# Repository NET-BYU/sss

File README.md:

# Seven Segment Sign

## Welcome to the Seven Segment Sign! (SSS)

## Getting Started
Here are some helpful links to get you up and running!
- [API Docs](https://sss.readthedocs.io/en/latest/API/Display/)
- [Install on Linux/Mac](https://sss.readthedocs.io/en/latest/Installation/Install%20SSS%20on%20Mac%20or%20Linux/)
- [Install on Windows](https://sss.readthedocs.io/en/latest/Installation/Install%20SSS%20on%20Windows/)
- [Create your first demo](https://sss.readthedocs.io/en/latest/Tutorials/Creating%20a%20demo/)

## Common Commands
Although thorough information on how to [get started](https://sss.readthedocs.io/en/latest/Overview/Get%20started/) is in the docs, here are some quick commands you can run in order to get rolling **once you have everything installed**:

- Run the PyGame Simulator for the SSS
  ```bash
  python3 main.py simulator
  ```
- Run a specific demo in the simulator
  ```bash
  python3 main.py demo <demo_name> -s
  ```
- Start the SSS in kiosk mode
  ```bash
  python3 main.py kiosk
  ```
- To view log output of varying degrees, use the `-v` option (the more `v`'s the more `v`erbose the output becomes

For any other help or a list of comprehensive commands, run
```bash
python3 main.py --help
```

## Reporting an Issue
We love feedback! As the SSS codespace expands and acquires new features, we realize that some bugs will fall through the cracks. Please feel free to open a new issue if you notice any bugs in the code, mistakes or missing information in the documentation, or if you want a new feature to be added to the project.

You can go to the **Issues** tab to create a new issue. Please be mindful to choose the correct template for the right type of question. Apart from the currently open issues from before this writing, any **issue that does not conform to the template may become stale or be closed without warning.**

## Submitting a PR
If you are feeling creative and you would like to contribute a demo but you are outside of our organization, you are more than welcome to submit a pull request and we will look it over! 

In order for a pull request to be merged, we have the following three policies:
1. Your code must have adequate, meaningful comments. Don't feel like you have to explain every statement, but also don't write comments like `# This a loop that goes over all the values`.
2. Your PR will need approval from **at least 2 org members**. Users who respond to these the most are @apal6981, @christopolise, and @philipbl
3. Your code **MUST** be formatted with `black`. This is as simple as adding the [Black Formatter](https://marketplace.visualstudio.com/items?itemName=ms-python.black-formatter) to VS/OSS Code or running `python3 -m black <your py files>`

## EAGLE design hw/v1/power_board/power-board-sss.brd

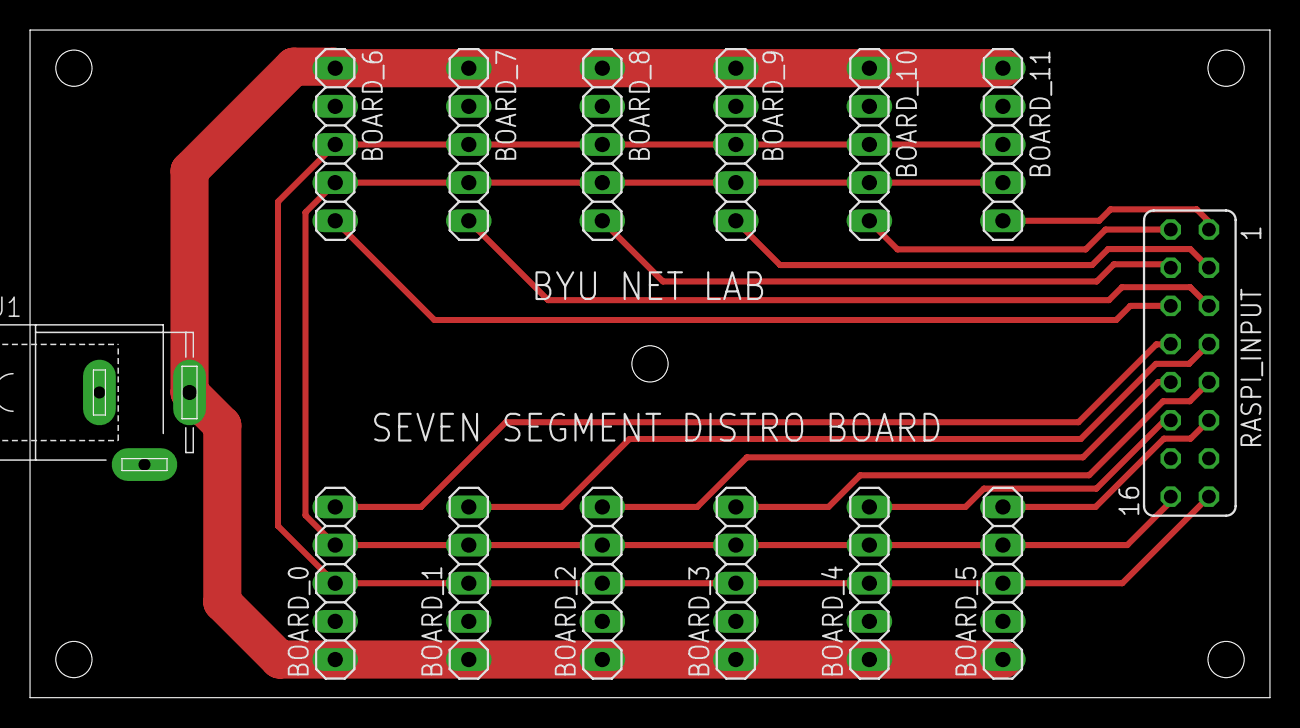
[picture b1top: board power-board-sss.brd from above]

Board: 2 copper layers, 82.5 x 44.5 mm, 14 parts (0 on the bottom side), 16 nets.

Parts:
BOARD_0, BOARD_1, BOARD_2, BOARD_3, BOARD_4, BOARD_5, BOARD_6, BOARD_7, BOARD_8, BOARD_9, BOARD_10, BOARD_11: 1X05
J1: SPC4078
RASPI_INPUT: FE08-2

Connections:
CLK: BOARD_0.3, BOARD_1.3, BOARD_2.3, BOARD_3.3, BOARD_4.3, BOARD_5.3, BOARD_6.3, BOARD_7.3, BOARD_8.3, BOARD_9.3, BOARD_10.3, BOARD_11.3, RASPI_INPUT.15
CS_0: BOARD_0.5, RASPI_INPUT.8
CS_1: BOARD_1.5, RASPI_INPUT.7
CS_2: BOARD_2.5, RASPI_INPUT.10
CS_3: BOARD_3.5, RASPI_INPUT.9
CS_4: BOARD_4.5, RASPI_INPUT.12
CS_5: BOARD_5.5, RASPI_INPUT.11
CS_6: BOARD_6.5, RASPI_INPUT.6
CS_7: BOARD_7.5, RASPI_INPUT.5
CS_8: BOARD_8.5, RASPI_INPUT.4
CS_9: BOARD_9.5, RASPI_INPUT.3
CS_10: BOARD_10.5, RASPI_INPUT.2
CS_11: BOARD_11.5, RASPI_INPUT.1
GND: BOARD_0.2, BOARD_1.2, BOARD_2.2, BOARD_3.2, BOARD_4.2, BOARD_5.2, BOARD_6.2, BOARD_7.2, BOARD_8.2, BOARD_9.2, BOARD_10.2, BOARD_11.2, J1.1, J1.2, RASPI_INPUT.13, RASPI_INPUT.14
MOSI: BOARD_0.4, BOARD_1.4, BOARD_2.4, BOARD_3.4, BOARD_4.4, BOARD_5.4, BOARD_6.4, BOARD_7.4, BOARD_8.4, BOARD_9.4, BOARD_10.4, BOARD_11.4, RASPI_INPUT.16
VCC: BOARD_0.1, BOARD_1.1, BOARD_2.1, BOARD_3.1, BOARD_4.1, BOARD_5.1, BOARD_6.1, BOARD_7.1, BOARD_8.1, BOARD_9.1, BOARD_10.1, BOARD_11.1, J1.3

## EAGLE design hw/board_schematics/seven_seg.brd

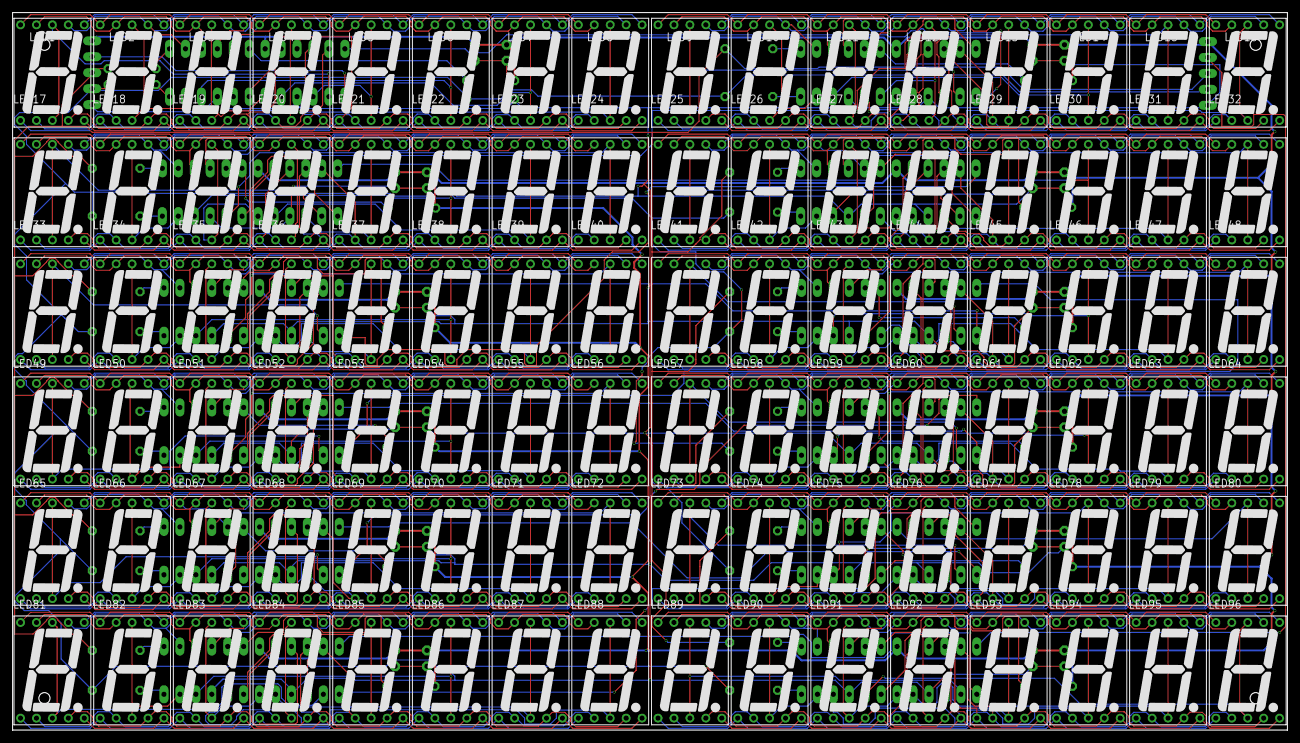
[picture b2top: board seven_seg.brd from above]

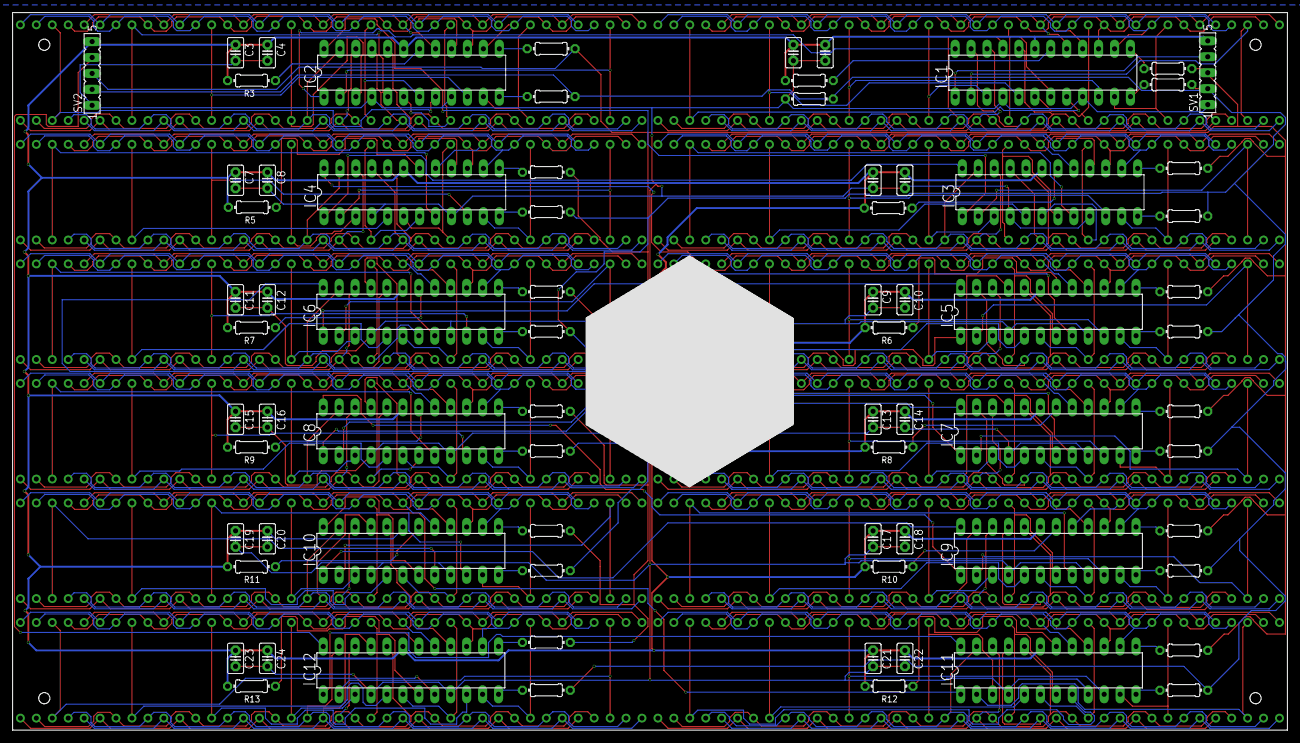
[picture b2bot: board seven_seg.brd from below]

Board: 2 copper layers, 203.2 x 114.3 mm, 171 parts (75 on the bottom side), 245 nets.

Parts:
C1, C3, C5, C7, C9, C11, C13, C15, C17, C19, C21, C23: 10uF; C2.5-2
C2, C4, C6, C8, C10, C12, C14, C16, C18, C20, C22, C24: 100nF; C2.5-2
IC1, IC2, IC3, IC4, IC5, IC6, IC7, IC8, IC9, IC10, IC11, IC12: MAX7219CNG; DIL24-3
LED1, LED2, LED3, LED4, LED5, LED6, LED7, LED8, LED9, LED10, LED11, LED12, LED13, LED14, LED15, LED16, LED17, LED18, LED19, LED20, LED21, LED22, LED23, LED24, LED25, LED26, LED27, LED28, LED29, LED30, LED31, LED32, LED33, LED34, LED35, LED36, LED37, LED38, LED39, LED40, LED41, LED42, LED43, LED44, LED45, LED46, LED47, LED48, LED49, LED50, LED51, LED52, LED53, LED54, LED55, LED56, LED57, LED58, LED59, LED60, LED61, LED62, LED63, LED64, LED65, LED66, LED67, LED68, LED69, LED70, LED71, LED72, LED73, LED74, LED75, LED76, LED77, LED78, LED79, LED80, LED81, LED82, LED83, LED84, LED85, LED86, LED87, LED88, LED89, LED90, LED91, LED92, LED93, LED94, LED95, LED96: 7-SEG_SA52-11; SA52-11
R1, R2, R3, R4, R5, R6, R7, R8, R9, R10, R11, R12, R13: 12k; 0204/7
R14, R15, R16, R17, R18, R19, R20, R21, R22, R23, R24, R25, R26, R27, R28, R29, R30, R31, R32, R33, R34, R35, R36, R37: 880; 0204/7
SV1, SV2: FE05-1

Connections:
CLK: R14.2, R16.2, R18.2, R20.2, R22.2, R24.2, R26.2, R28.2, R30.2, R32.2, R34.2, R36.2, SV1.3, SV2.3
DIN: IC1.1, SV1.4
GND: C1.2, C2.2, C3.2, C4.2, C5.2, C6.2, C7.2, C8.2, C9.2, C10.2, C11.2, C12.2, C13.2, C14.2, C15.2, C16.2, C17.2, C18.2, C19.2, C20.2, C21.2, C22.2, C23.2, C24.2, IC1.4, IC1.9, IC2.4, IC2.9, IC3.4, IC3.9, IC4.4, IC4.9, IC5.4, IC5.9, IC6.4, IC6.9, IC7.4, IC7.9, IC8.4, IC8.9, IC9.4, IC9.9, IC10.4, IC10.9, IC11.4, IC11.9, IC12.4, IC12.9, R2.1, SV1.1, SV2.1
LOAD: R2.2, R15.2, R17.2, R19.2, R21.2, R23.2, R25.2, R27.2, R29.2, R31.2, R33.2, R35.2, R37.2, SV1.2, SV2.2
unnamed: IC1.2, LED1.3, LED1.8
unnamed: IC1.11, LED2.3, LED2.8
unnamed: IC1.6, LED3.3, LED3.8
unnamed: IC1.7, LED4.3, LED4.8
unnamed: IC1.3, LED5.3, LED5.8
unnamed: IC1.10, LED6.3, LED6.8
unnamed: IC1.5, LED7.3, LED7.8
unnamed: IC1.8, LED8.3, LED8.8
unnamed: IC1.15, LED1.9, LED2.9, LED3.9, LED4.9, LED5.9, LED6.9, LED7.9, LED8.9
unnamed: IC2.18, R3.2
unnamed: IC2.22, LED9.5, LED10.5, LED11.5, LED12.5, LED13.5, LED14.5, LED15.5, LED16.5
unnamed: IC1.13, R14.1
unnamed: IC1.12, R15.1
unnamed: IC2.13, R16.1
unnamed: IC2.2, LED9.3, LED9.8
unnamed: IC1.18, R1.2
unnamed: IC1.14, LED1.7, LED2.7, LED3.7, LED4.7, LED5.7, LED6.7, LED7.7, LED8.7
unnamed: IC1.22, LED1.5, LED2.5, LED3.5, LED4.5, LED5.5, LED6.5, LED7.5, LED8.5
unnamed: IC1.16, LED1.6, LED2.6, LED3.6, LED4.6, LED5.6, LED6.6, LED7.6, LED8.6
unnamed: IC1.20, LED1.4, LED2.4, LED3.4, LED4.4, LED5.4, LED6.4, LED7.4, LED8.4
unnamed: IC1.23, LED1.2, LED2.2, LED3.2, LED4.2, LED5.2, LED6.2, LED7.2, LED8.2
unnamed: IC1.21, LED1.1, LED2.1, LED3.1, LED4.1, LED5.1, LED6.1, LED7.1, LED8.1
unnamed: IC2.11, LED10.3, LED10.8
unnamed: IC1.17, LED1.10, LED2.10, LED3.10, LED4.10, LED5.10, LED6.10, LED7.10, LED8.10
unnamed: IC2.6, LED11.3, LED11.8
unnamed: IC2.7, LED12.3, LED12.8
unnamed: IC2.3, LED13.3, LED13.8
unnamed: IC2.10, LED14.3, LED14.8
unnamed: IC2.5, LED15.3, LED15.8
unnamed: IC2.8, LED16.3, LED16.8
unnamed: IC2.14, LED9.7, LED10.7, LED11.7, LED12.7, LED13.7, LED14.7, LED15.7, LED16.7
unnamed: IC2.16, LED9.6, LED10.6, LED11.6, LED12.6, LED13.6, LED14.6, LED15.6, LED16.6
unnamed: IC2.20, LED9.4, LED10.4, LED11.4, LED12.4, LED13.4, LED14.4, LED15.4, LED16.4
unnamed: IC2.23, LED9.2, LED10.2, LED11.2, LED12.2, LED13.2, LED14.2, LED15.2, LED16.2
unnamed: IC2.21, LED9.1, LED10.1, LED11.1, LED12.1, LED13.1, LED14.1, LED15.1, LED16.1
unnamed: IC2.17, LED9.10, LED10.10, LED11.10, LED12.10, LED13.10, LED14.10, LED15.10, LED16.10
unnamed: IC2.15, LED9.9, LED10.9, LED11.9, LED12.9, LED13.9, LED14.9, LED15.9, LED16.9
unnamed: IC2.24, IC3.1
unnamed: IC10.3, LED77.3, LED77.8
unnamed: IC2.12, R17.1
unnamed: IC3.13, R18.1
unnamed: IC1.24, IC2.1
unnamed: IC3.12, R19.1
unnamed: IC4.13, R20.1
unnamed: IC4.12, R21.1
unnamed: IC3.18, R4.2
unnamed: IC3.22, LED17.5, LED18.5, LED19.5, LED20.5, LED21.5, LED22.5, LED23.5, LED24.5
unnamed: IC3.2, LED17.3, LED17.8
unnamed: IC3.11, LED18.3, LED18.8
unnamed: IC3.6, LED19.3, LED19.8
unnamed: IC3.7, LED20.3, LED20.8
unnamed: IC3.3, LED21.3, LED21.8
unnamed: IC3.10, LED22.3, LED22.8
unnamed: IC3.5, LED23.3, LED23.8
unnamed: IC3.8, LED24.3, LED24.8
unnamed: IC3.14, LED17.7, LED18.7, LED19.7, LED20.7, LED21.7, LED22.7, LED23.7, LED24.7
unnamed: IC3.16, LED17.6, LED18.6, LED19.6, LED20.6, LED21.6, LED22.6, LED23.6, LED24.6
unnamed: IC3.20, LED17.4, LED18.4, LED19.4, LED20.4, LED21.4, LED22.4, LED23.4, LED24.4
unnamed: IC3.23, LED17.2, LED18.2, LED19.2, LED20.2, LED21.2, LED22.2, LED23.2, LED24.2
unnamed: IC3.21, LED17.1, LED18.1, LED19.1, LED20.1, LED21.1, LED22.1, LED23.1, LED24.1
unnamed: IC3.17, LED17.10, LED18.10, LED19.10, LED20.10, LED21.10, LED22.10, LED23.10, LED24.10
unnamed: IC3.15, LED17.9, LED18.9, LED19.9, LED20.9, LED21.9, LED22.9, LED23.9, LED24.9
unnamed: IC5.13, R22.1
unnamed: IC5.12, R23.1
unnamed: IC6.13, R24.1
unnamed: IC4.18, R5.2
unnamed: IC3.24, IC4.1
unnamed: IC4.22, LED25.5, LED26.5, LED27.5, LED28.5, LED29.5, LED30.5, LED31.5, LED32.5
unnamed: IC4.2, LED25.3, LED25.8
unnamed: IC4.11, LED26.3, LED26.8
unnamed: IC4.6, LED27.3, LED27.8
unnamed: IC4.7, LED28.3, LED28.8
unnamed: IC4.3, LED29.3, LED29.8
unnamed: IC4.10, LED30.3, LED30.8
unnamed: IC4.5, LED31.3, LED31.8
unnamed: IC4.8, LED32.3, LED32.8
unnamed: IC4.14, LED25.7, LED26.7, LED27.7, LED28.7, LED29.7, LED30.7, LED31.7, LED32.7
unnamed: IC4.16, LED25.6, LED26.6, LED27.6, LED28.6, LED29.6, LED30.6, LED31.6, LED32.6
unnamed: IC4.20, LED25.4, LED26.4, LED27.4, LED28.4, LED29.4, LED30.4, LED31.4, LED32.4
unnamed: IC4.23, LED25.2, LED26.2, LED27.2, LED28.2, LED29.2, LED30.2, LED31.2, LED32.2
unnamed: IC4.21, LED25.1, LED26.1, LED27.1, LED28.1, LED29.1, LED30.1, LED31.1, LED32.1
unnamed: IC4.17, LED25.10, LED26.10, LED27.10, LED28.10, LED29.10, LED30.10, LED31.10, LED32.10
unnamed: IC4.15, LED25.9, LED26.9, LED27.9, LED28.9, LED29.9, LED30.9, LED31.9, LED32.9
unnamed: IC6.12, R25.1
unnamed: IC4.24, IC5.1
unnamed: IC7.13, R26.1
unnamed: IC7.12, R27.1
unnamed: IC8.13, R28.1
unnamed: IC8.12, R29.1
unnamed: IC9.13, R30.1
unnamed: IC5.18, R6.2
unnamed: IC5.22, LED33.5, LED34.5, LED35.5, LED36.5, LED37.5, LED38.5, LED39.5, LED40.5
unnamed: IC5.2, LED33.3, LED33.8
unnamed: IC5.11, LED34.3, LED34.8
unnamed: IC5.6, LED35.3, LED35.8
unnamed: IC5.7, LED36.3, LED36.8
unnamed: IC5.3, LED37.3, LED37.8
unnamed: IC5.10, LED38.3, LED38.8
unnamed: IC5.5, LED39.3, LED39.8
unnamed: IC5.8, LED40.3, LED40.8
unnamed: IC5.14, LED33.7, LED34.7, LED35.7, LED36.7, LED37.7, LED38.7, LED39.7, LED40.7
unnamed: IC5.16, LED33.6, LED34.6, LED35.6, LED36.6, LED37.6, LED38.6, LED39.6, LED40.6
unnamed: IC5.20, LED33.4, LED34.4, LED35.4, LED36.4, LED37.4, LED38.4, LED39.4, LED40.4
unnamed: IC5.23, LED33.2, LED34.2, LED35.2, LED36.2, LED37.2, LED38.2, LED39.2, LED40.2
unnamed: IC5.21, LED33.1, LED34.1, LED35.1, LED36.1, LED37.1, LED38.1, LED39.1, LED40.1
unnamed: IC5.17, LED33.10, LED34.10, LED35.10, LED36.10, LED37.10, LED38.10, LED39.10, LED40.10
unnamed: IC5.15, LED33.9, LED34.9, LED35.9, LED36.9, LED37.9, LED38.9, LED39.9, LED40.9
unnamed: IC9.12, R31.1
unnamed: IC5.24, IC6.1
unnamed: IC10.13, R32.1
unnamed: IC10.12, R33.1
unnamed: IC11.13, R34.1
unnamed: IC11.12, R35.1
unnamed: IC12.13, R36.1
unnamed: IC6.18, R7.2
unnamed: IC6.22, LED41.5, LED42.5, LED43.5, LED44.5, LED45.5, LED46.5, LED47.5, LED48.5
unnamed: IC6.2, LED41.3, LED41.8
unnamed: IC6.11, LED42.3, LED42.8
unnamed: IC6.6, LED43.3, LED43.8
unnamed: IC6.7, LED44.3, LED44.8
unnamed: IC6.3, LED45.3, LED45.8
unnamed: IC6.10, LED46.3, LED46.8
unnamed: IC6.5, LED47.3, LED47.8
unnamed: IC6.8, LED48.3, LED48.8
unnamed: IC6.14, LED41.7, LED42.7, LED43.7, LED44.7, LED45.7, LED46.7, LED47.7, LED48.7
unnamed: IC6.16, LED41.6, LED42.6, LED43.6, LED44.6, LED45.6, LED46.6, LED47.6, LED48.6
unnamed: IC6.20, LED41.4, LED42.4, LED43.4, LED44.4, LED45.4, LED46.4, LED47.4, LED48.4
unnamed: IC6.23, LED41.2, LED42.2, LED43.2, LED44.2, LED45.2, LED46.2, LED47.2, LED48.2
unnamed: IC6.21, LED41.1, LED42.1, LED43.1, LED44.1, LED45.1, LED46.1, LED47.1, LED48.1
unnamed: IC6.17, LED41.10, LED42.10, LED43.10, LED44.10, LED45.10, LED46.10, LED47.10, LED48.10
unnamed: IC6.15, LED41.9, LED42.9, LED43.9, LED44.9, LED45.9, LED46.9, LED47.9, LED48.9
unnamed: IC12.12, R37.1
unnamed: IC6.24, IC7.1
unnamed: IC7.18, R8.2
unnamed: IC7.22, LED49.5, LED50.5, LED51.5, LED52.5, LED53.5, LED54.5, LED55.5, LED56.5
unnamed: IC7.2, LED49.3, LED49.8
unnamed: IC7.11, LED50.3, LED50.8
unnamed: IC7.6, LED51.3, LED51.8
unnamed: IC7.7, LED52.3, LED52.8
unnamed: IC7.3, LED53.3, LED53.8
unnamed: IC7.10, LED54.3, LED54.8
unnamed: IC7.5, LED55.3, LED55.8
unnamed: IC7.8, LED56.3, LED56.8
unnamed: IC7.14, LED49.7, LED50.7, LED51.7, LED52.7, LED53.7, LED54.7, LED55.7, LED56.7
unnamed: IC7.16, LED49.6, LED50.6, LED51.6, LED52.6, LED53.6, LED54.6, LED55.6, LED56.6
unnamed: IC7.20, LED49.4, LED50.4, LED51.4, LED52.4, LED53.4, LED54.4, LED55.4, LED56.4
unnamed: IC7.23, LED49.2, LED50.2, LED51.2, LED52.2, LED53.2, LED54.2, LED55.2, LED56.2
unnamed: IC7.21, LED49.1, LED50.1, LED51.1, LED52.1, LED53.1, LED54.1, LED55.1, LED56.1
unnamed: IC7.17, LED49.10, LED50.10, LED51.10, LED52.10, LED53.10, LED54.10, LED55.10, LED56.10
unnamed: IC7.15, LED49.9, LED50.9, LED51.9, LED52.9, LED53.9, LED54.9, LED55.9, LED56.9
unnamed: IC7.24, IC8.1
unnamed: IC8.18, R9.2
unnamed: IC8.22, LED57.5, LED58.5, LED59.5, LED60.5, LED61.5, LED62.5, LED63.5, LED64.5
unnamed: IC8.2, LED57.3, LED57.8
unnamed: IC8.11, LED58.3, LED58.8
unnamed: IC8.6, LED59.3, LED59.8
unnamed: IC8.7, LED60.3, LED60.8
unnamed: IC8.3, LED61.3, LED61.8
unnamed: IC8.10, LED62.3, LED62.8
unnamed: IC8.5, LED63.3, LED63.8
unnamed: IC8.8, LED64.3, LED64.8
unnamed: IC8.14, LED57.7, LED58.7, LED59.7, LED60.7, LED61.7, LED62.7, LED63.7, LED64.7
unnamed: IC8.16, LED57.6, LED58.6, LED59.6, LED60.6, LED61.6, LED62.6, LED63.6, LED64.6
unnamed: IC8.20, LED57.4, LED58.4, LED59.4, LED60.4, LED61.4, LED62.4, LED63.4, LED64.4
unnamed: IC8.23, LED57.2, LED58.2, LED59.2, LED60.2, LED61.2, LED62.2, LED63.2, LED64.2
unnamed: IC8.21, LED57.1, LED58.1, LED59.1, LED60.1, LED61.1, LED62.1, LED63.1, LED64.1
unnamed: IC8.17, LED57.10, LED58.10, LED59.10, LED60.10, LED61.10, LED62.10, LED63.10, LED64.10
unnamed: IC8.15, LED57.9, LED58.9, LED59.9, LED60.9, LED61.9, LED62.9, LED63.9, LED64.9
unnamed: IC8.24, IC9.1
unnamed: IC12.18, R13.2
unnamed: IC9.18, R10.2
unnamed: IC9.22, LED65.5, LED66.5, LED67.5, LED68.5, LED69.5, LED70.5, LED71.5, LED72.5
unnamed: IC9.2, LED65.3, LED65.8
unnamed: IC9.11, LED66.3, LED66.8
unnamed: IC9.6, LED67.3, LED67.8
unnamed: IC9.7, LED68.3, LED68.8
unnamed: IC9.3, LED69.3, LED69.8
unnamed: IC9.10, LED70.3, LED70.8
unnamed: IC9.5, LED71.3, LED71.8
unnamed: IC9.8, LED72.3, LED72.8
unnamed: IC9.14, LED65.7, LED66.7, LED67.7, LED68.7, LED69.7, LED70.7, LED71.7, LED72.7
unnamed: IC9.16, LED65.6, LED66.6, LED67.6, LED68.6, LED69.6, LED70.6, LED71.6, LED72.6
unnamed: IC9.20, LED65.4, LED66.4, LED67.4, LED68.4, LED69.4, LED70.4, LED71.4, LED72.4
unnamed: IC9.23, LED65.2, LED66.2, LED67.2, LED68.2, LED69.2, LED70.2, LED71.2, LED72.2
unnamed: IC9.21, LED65.1, LED66.1, LED67.1, LED68.1, LED69.1, LED70.1, LED71.1, LED72.1
unnamed: IC9.17, LED65.10, LED66.10, LED67.10, LED68.10, LED69.10, LED70.10, LED71.10, LED72.10
unnamed: IC9.15, LED65.9, LED66.9, LED67.9, LED68.9, LED69.9, LED70.9, LED71.9, LED72.9
unnamed: IC9.24, IC10.1
unnamed: IC12.22, LED89.5, LED90.5, LED91.5, LED92.5, LED93.5, LED94.5, LED95.5, LED96.5
unnamed: IC12.2, LED89.3, LED89.8
unnamed: IC12.11, LED90.3, LED90.8
unnamed: IC12.6, LED91.3, LED91.8
unnamed: IC12.7, LED92.3, LED92.8
unnamed: IC10.18, R11.2
unnamed: IC10.22, LED73.5, LED74.5, LED75.5, LED76.5, LED77.5, LED78.5, LED79.5, LED80.5
unnamed: IC10.2, LED73.3, LED73.8
unnamed: IC10.11, LED74.3, LED74.8
unnamed: IC10.6, LED75.3, LED75.8
unnamed: IC10.7, LED76.3, LED76.8
unnamed: IC10.10, LED78.3, LED78.8
unnamed: IC10.5, LED79.3, LED79.8
unnamed: IC10.8, LED80.3, LED80.8
unnamed: IC10.14, LED73.7, LED74.7, LED75.7, LED76.7, LED77.7, LED78.7, LED79.7, LED80.7
unnamed: IC10.16, LED73.6, LED74.6, LED75.6, LED76.6, LED77.6, LED78.6, LED79.6, LED80.6
unnamed: IC10.20, LED73.4, LED74.4, LED75.4, LED76.4, LED77.4, LED78.4, LED79.4, LED80.4
unnamed: IC10.23, LED73.2, LED74.2, LED75.2, LED76.2, LED77.2, LED78.2, LED79.2, LED80.2
unnamed: IC10.21, LED73.1, LED74.1, LED75.1, LED76.1, LED77.1, LED78.1, LED79.1, LED80.1
unnamed: IC10.17, LED73.10, LED74.10, LED75.10, LED76.10, LED77.10, LED78.10, LED79.10, LED80.10
unnamed: IC10.15, LED73.9, LED74.9, LED75.9, LED76.9, LED77.9, LED78.9, LED79.9, LED80.9
unnamed: IC10.24, IC11.1
unnamed: IC12.3, LED93.3, LED93.8
unnamed: IC12.10, LED94.3, LED94.8
unnamed: IC12.5, LED95.3, LED95.8
unnamed: IC12.8, LED96.3, LED96.8
unnamed: IC12.14, LED89.7, LED90.7, LED91.7, LED92.7, LED93.7, LED94.7, LED95.7, LED96.7
unnamed: IC11.18, R12.2
unnamed: IC11.22, LED81.5, LED82.5, LED83.5, LED84.5, LED85.5, LED86.5, LED87.5, LED88.5
unnamed: IC11.2, LED81.3, LED81.8
unnamed: IC11.11, LED82.3, LED82.8
unnamed: IC11.6, LED83.3, LED83.8
unnamed: IC11.7, LED84.3, LED84.8
unnamed: IC11.3, LED85.3, LED85.8
unnamed: IC11.10, LED86.3, LED86.8
unnamed: IC11.5, LED87.3, LED87.8
unnamed: IC11.8, LED88.3, LED88.8
unnamed: IC11.14, LED81.7, LED82.7, LED83.7, LED84.7, LED85.7, LED86.7, LED87.7, LED88.7
unnamed: IC11.16, LED81.6, LED82.6, LED83.6, LED84.6, LED85.6, LED86.6, LED87.6, LED88.6
unnamed: IC11.20, LED81.4, LED82.4, LED83.4, LED84.4, LED85.4, LED86.4, LED87.4, LED88.4
unnamed: IC11.23, LED81.2, LED82.2, LED83.2, LED84.2, LED85.2, LED86.2, LED87.2, LED88.2
unnamed: IC11.21, LED81.1, LED82.1, LED83.1, LED84.1, LED85.1, LED86.1, LED87.1, LED88.1
unnamed: IC11.17, LED81.10, LED82.10, LED83.10, LED84.10, LED85.10, LED86.10, LED87.10, LED88.10
unnamed: IC11.15, LED81.9, LED82.9, LED83.9, LED84.9, LED85.9, LED86.9, LED87.9, LED88.9
unnamed: IC11.24, IC12.1
unnamed: IC12.16, LED89.6, LED90.6, LED91.6, LED92.6, LED93.6, LED94.6, LED95.6, LED96.6
unnamed: IC12.20, LED89.4, LED90.4, LED91.4, LED92.4, LED93.4, LED94.4, LED95.4, LED96.4
unnamed: IC12.23, LED89.2, LED90.2, LED91.2, LED92.2, LED93.2, LED94.2, LED95.2, LED96.2
unnamed: IC12.21, LED89.1, LED90.1, LED91.1, LED92.1, LED93.1, LED94.1, LED95.1, LED96.1
unnamed: IC12.17, LED89.10, LED90.10, LED91.10, LED92.10, LED93.10, LED94.10, LED95.10, LED96.10
unnamed: IC12.15, LED89.9, LED90.9, LED91.9, LED92.9, LED93.9, LED94.9, LED95.9, LED96.9
unnamed: IC12.24, SV2.4
VCC: C1.1, C2.1, C3.1, C4.1, C5.1, C6.1, C7.1, C8.1, C9.1, C10.1, C11.1, C12.1, C13.1, C14.1, C15.1, C16.1, C17.1, C18.1, C19.1, C20.1, C21.1, C22.1, C23.1, C24.1, IC1.19, IC2.19, IC3.19, IC4.19, IC5.19, IC6.19, IC7.19, IC8.19, IC9.19, IC10.19, IC11.19, IC12.19, R1.1, R3.1, R4.1, R5.1, R6.1, R7.1, R8.1, R9.1, R10.1, R11.1, R12.1, R13.1, SV1.5, SV2.5

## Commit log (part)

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2022-06-27 Fix bug in kiosk with setting demo time
2022-06-27 Fixing 'NO CAMERA' being stuck on the screen
2022-06-28 Format all code using black
2022-06-28 Hotfix for requirements.txt
2022-06-28 Remove comments of testing
2022-06-28 Testing error type
2022-06-28 Clean up requirements
2022-06-28 Move import error and disable keyboard
2022-06-29 Move try except to keyboard.py
2022-06-29 Return none to disable keyboard
2022-06-29 Cleanup log output
2022-06-30 Add self-hosted action to check on a Raspberry Pi
    This will run the test suite on the Raspberry Pi to make sure it runs
    properly on the correct hardware.
2022-06-30 Improve testing script
2022-06-30 Camera punished
2022-06-30 Add pylint configuration file
2022-06-30 Fix error with importing pygame
    Moved imports around so that pygame is not accidentally imported when
    running tests.
2022-07-01 Hold on
2022-07-01 No one wants this
2022-07-05 Refresh display between user selected demos
2022-07-05 fixed restarting bug
2022-07-05 fixing up the snake game and snake ai demo
2022-07-05 changed logger statements to debug status
2022-07-05 reran black, setting line length to 100 did weird things upstream
2022-07-06 Add keymap for more buttons, added output stream from doom
2022-07-06 Enable output logging
2022-07-07 Added broadcaster module
2022-07-07 Fix logic behind reading queue
2022-07-07 Checked in kiosk and fixed ai
2022-07-07 No broadcasters for simulator...ask @apal6981
2022-07-07 Start game and manage the memory
2022-07-07 Readme cleanup
2022-07-07 Now will avoid looking for a camera that is disconnected
2022-07-08 Add verbose flag to CLI
2022-07-08 Specify sysv-ipc version
2022-07-08 Guard statement instead of static while
2022-07-08 Added an interesting level
2022-07-08 Better lighting levels
2022-07-08 Different color sorting
2022-07-08 Better WAD
2022-07-09 Remove line from simulator
2022-07-09 Fix style of passing out message to broadcasters
2022-07-11 Add isort to formatting action
2022-07-12 Handle keyboard interrupts
2022-07-12 Refactor
2022-07-12 Refactor code
    Put Queues data class into utils
2022-07-14 Update theme and requirements
2022-07-14 Start of intro
2022-07-14 Intro is landing?
2022-07-14 Fix intro and add support
2022-07-14 Fixed light-dark mode toggle
2022-07-14 Fix html injection line
2022-07-19 Clear screen after stopping demo
2022-07-19 Handle keyboard interrupt in simulator
2022-07-28 Suppress game output, status message for end added
2022-08-10 Some comments and docs for installing
2022-08-10 about the team
2022-08-12 Add device tree assets
2022-08-12 Finished GPIO article
2022-08-12 Another method
2022-08-12 Its not pretty but there it is
2022-08-12 Reorganize hardwire files
2022-08-12 Finished camera documentation
2022-08-12 Finished enclosure and feet sans 3mf
2022-08-12 More schematics and brd images added
2022-08-13 Finished FAQs
2022-08-13 Transparency images fixed
2022-08-16 Panel article
2022-08-16 Panels
2022-08-17 Windows notes
2022-08-18 Set default version to latest with mike 1.1.2
2022-08-18 Test versioning
2022-08-18 Added dropdown
2022-08-18 Remove hard ref
2022-08-18 restart sss rtfd
2022-08-18 Update to incorporate sss rtfd
2022-09-01 Hotfix that prevents issue #25
2022-09-08 Handle exceptions when playing demo in kiosk mode
2023-03-15 News section in docs
2023-03-21 test formatting
2023-03-21 reformat offending files
2023-03-21 Forgot some
2023-05-05 Basic draft with multiple screens of definitions
2023-05-05 Tweaked output format
2023-05-05 Added definitions
2023-05-24 Update news
2023-06-09 Added new link and removed site folder tracking
2023-06-13 Recursive zero finding works
2023-06-13 Added flag drawing logic
2023-06-14 Game win/lose logic set. Pending repeat direction arrows
2023-06-14 Fix game over logic
2023-08-21 init of two_circle
2023-08-22 Added new code for a two pixel circle display, to a new branch
2023-08-24 Clarify virtual environment indicator
2023-08-24 Fix internal link #33
2023-08-24 Fix comments to be compatible with mkdocstring #34
2023-08-25 Add some new comments
2023-08-25 Decided to split movement into separate functions. made a new branch
2023-08-28 single panel debug
2023-08-28 More detailed and formatted docs for broadcasters and controllers
2023-08-29 fixed the demo and some print statements
2023-08-29 removed the asdf from video demo
2023-08-30 Some work done, still struggling
2023-08-30 Yes, this is bad juju, but it fixes the build
2023-08-30 Fix format issue
2023-08-30 Added shrek and better formatting
2023-08-30 Debug again
2023-08-30 Found the bugger
2023-08-31 Hot mess
2023-08-31 Debug drawing speed
2023-08-31 Trying to fit formatting requirements better
2023-08-31 Fix formatting
2023-08-31 Fix formatting ++
2023-08-31 init
2023-08-31 Adding pygame-mixer sound broadcaster
2023-08-31 Update issue templates
    This provides templates to make it easier for users/developers to describe what is going wrong and how it can be addressed
2023-08-31 Some sounds don't work, removing them
2023-09-01 Fixing formatting
2023-09-01 Fixing slight sound delay
2023-09-01 Snake sounds
2023-09-01 Adding a ton of new sounds
2023-09-01 Fixed skipping videos that have already been processed'
2023-09-01 Fixing and adding some things
2023-09-01 Formatting welcome_y
2023-09-01 creating a place for bryson to work his magic
2023-09-01 Adding sully sound
2023-09-01 Tetris clear row sound
2023-09-01 added sounds to movement
2023-09-01 Adding Nyan Cat sound
2023-09-01 Formatting video sound
2023-09-01 Quic under_construction
2023-09-01 Rick was having some issues but I fixed them
2023-10-18 Bump urllib3 from 1.26.9 to 1.26.18
    Bumps [urllib3](https://github.com/urllib3/urllib3) from 1.26.9 to 1.26.18.
    - [Release notes](https://github.com/urllib3/urllib3/releases)
    - [Changelog](https://github.com/urllib3/urllib3/blob/main/CHANGES.rst)
    - [Commits](https://github.com/urllib3/urllib3/compare/1.26.9...1.26.18)
    ---
    updated-dependencies:
2024-04-12 Adding a few sounds
2024-08-19 Fixing minor issue in hangman_ai, changing is_not to != to remove warning
2024-08-19 Bump black from 22.6.0 to 24.3.0
    Bumps [black](https://github.com/psf/black) from 22.6.0 to 24.3.0.
    - [Release notes](https://github.com/psf/black/releases)
    - [Changelog](https://github.com/psf/black/blob/main/CHANGES.md)
    - [Commits](https://github.com/psf/black/compare/22.6.0...24.3.0)
    ---
    updated-dependencies:
2024-08-19 Run formatter
2024-08-19 Maze builds alright
2024-08-19 Main gameplay is working
2024-08-19 Trying to use sounds with maze
2024-08-20 Working on prints
2024-08-23 Figure out python environment
2024-08-23 Test something else out
2024-08-23 Try more stuff
2024-08-23 More stuff
2024-08-31 Bump opencv-python from 4.6.0.66 to 4.8.1.78
    Bumps [opencv-python](https://github.com/opencv/opencv-python) from 4.6.0.66 to 4.8.1.78.
    - [Release notes](https://github.com/opencv/opencv-python/releases)
    - [Commits](https://github.com/opencv/opencv-python/commits)
    ---
    updated-dependencies:
    - dependency-name: opencv-python
2024-10-22 Fix ai stuck in loop
2024-10-22 Fix import sorting
2024-10-22 Fix formatting and comments
2024-10-23 Try to set up python version
2024-10-23 More testing
2024-10-23 Keep on fixing...
2024-10-23 Test normal tester
2024-10-23 Fix problem with using pyenv
2024-10-23 Update openCV
2024-10-23 Update pyyaml
2024-10-23 Test more python versions
2024-10-23 Update versions of actions
2024-10-23 Raise more descriptive error when text is too long
    Fixes #36
2024-10-23 Added docstrings for pretty much everything
2024-10-23 Fixed tetris error
2024-10-23 Fixed circle error
2024-10-23 Make a little cleaner
2024-10-23 Lets try this again
2024-10-23 Update rules hotfix
2024-10-23 Maybe this will help
2024-10-23 Pkt upgrades
2024-10-23 I'm getting lazier
2024-10-23 I'm so done with this junk
2024-10-23 Added runner docs
2024-10-23 Reformat with isort
2024-10-23 Fix isort issues
2024-10-24 Fix @philipbl knitpick
2024-10-24 hotfix to snake ai crashing and not displaying a banner when restarting
2024-10-25 Only print logs if controllers are there
2024-10-25 Fix logo placement for flag as ref'd in #67
2024-10-25 Add sound broadcaster
2024-10-25 Fix imports
2024-10-25 Fix the order of the demos
2024-10-31 adding v2 hardware
2024-10-31 formatted
2024-10-31 cleaned up some constants and comments
2024-10-31 Add initial menu system while in kiosk mode
2024-10-31 Fix problem with breakout taking all input from q
2024-10-31 Change the button to select the demo
2024-10-31 Center title
2024-11-01 changed dependency on pygame, only loads when screen is being simulated
2024-11-01 formated with black
2024-11-01 Fix typo
2024-11-01 Change the way transitions happen between menu
    Previously I was detecting items in the demo queue. I changed it to
    detect SEL or SEC in the system queue. This made the logic way eaiser.
2024-11-01 Change to a better trigger key press
2024-11-01 renamed files and newhardware variable -> new_hardware
2024-11-03 Handle if the system input queue is not provided
2024-11-03 No longer require demos to be passed into demo
2024-11-03 Fix formatting
    isort and black are disagreeing and I don't have the time to figure
    out why.
2024-11-05 Fix bug with N key being put on the system queue
2024-12-17 Initial drawing and sprites for dino run
2024-12-17 Jumping seems to be working
2024-12-18 Correct refactoring for classes
2024-12-21 figuring out timer for jumping and running animation
2024-12-27 remove classes and added dicts for objs
2024-12-28 Dumb hack that fixes drawing for screen
2024-12-28 Pretty sure this mostly works, todo: collision refine and dynamic difficulty
2024-12-28 Auto creation of high score file if one does not exist
2024-12-28 Yeah no idea how to format at this point
2024-12-30 Dynamic difficulty added
2025-02-24 moved RPi/linux specific dependencies into its own requirements, they were breaking windows
2025-02-24 fixed linux specific python path programming, now the simulator works on windows
2025-02-25 black
2025-02-25 ran isort correctly??
2025-02-25 rearrange hw folder and add v2 pcb
2025-02-25 added firmware for v2 board
2025-04-08 committing stuff from forever ago, maybe won't work
2025-04-08 Creating pinball main
2025-05-25 gitignore update
2025-05-26 Changed simluator to add different color of digits that can be changed with a click of button.
2025-06-21 Saving to work on something else
2025-06-27 added prusa demo
2025-08-29 Update to support big screen
2025-08-29 Add presentation mode
2025-08-29 Make the demos a little tighter
2025-11-14 Fix black error
2025-11-14 Use only log files
    No longer print log messages to stderr
2025-11-14 Set default logging level to INFO
    Changed the logger_level array to start with INFO instead of ERROR,
    making INFO the default logging level when no verbose flags are used.
    This ensures users see important operational messages (including the
    ASCII art banner) without needing to pass -vvv.
    The new verbosity levels are:
    - Default (no flags): INFO
2025-11-14 fix black formatting
2025-11-15 Use pygame to play a sound
2025-11-15 Update sound demo refresh rate
    Helps with playing the sounds faster
2025-11-18 Clean up CI
    - Add new Python version
    - Remove Pi runner until it is ready...
2025-11-21 Fix address and debug demo added
2025-12-06 Bump urllib3 from 2.5.0 to 2.6.0
    Bumps [urllib3](https://github.com/urllib3/urllib3) from 2.5.0 to 2.6.0.
    - [Release notes](https://github.com/urllib3/urllib3/releases)
    - [Changelog](https://github.com/urllib3/urllib3/blob/main/CHANGES.rst)
    - [Commits](https://github.com/urllib3/urllib3/compare/2.5.0...2.6.0)
    ---
    updated-dependencies:
2025-12-19 Add configuration file for creating v2 display
